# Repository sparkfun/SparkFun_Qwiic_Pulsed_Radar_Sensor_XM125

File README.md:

SparkFun Pulsed Coherent Radar Sensor - Acconeer XM125 (Qwiic)
========================================

[*SparkFun Pulsed Coherent Radar Sensor – Acconeer XM125 (Qwiic) (SEN-24540)*](https://www.sparkfun.com/products/24540)

Forget ultrasonic and infrared sensors; the SparkFun Qwiic Pulsed Coherent Radar Sensor - Acconeer XM125 brings powerful 60 GHz radar technology to your projects. This sensor isn't limited to surface detection; it can see through walls, cabinets, and even pockets (depending on the material), making it perfect for unique applications. Measure distances with millimeter precision, detect motion, the speed of an object, or even gestures!

The XM125 boasts an impressive range of up to 20 meters, allowing you to create long-range sensing projects. The actual measurable distance is dependent on the object size, shape, dielectric properties, and lens (e.g. water level measurements up to 20 meters with lens utilization, human presence detection up to 7 meters with lens-free utilization). Despite its power, the sensor has remarkably low in power consumption, which is ideal for battery-powered applications. The real magic lies in the sensor's ability to do more than measure distance; the XM125 can differentiate between stationary objects and moving targets using pulsed coherent radar. This means you can sense an object's presence and how fast something is moving!

We've included a USB type-C connector, ESD protection diodes on the USB data lines, and a CH340C USB-to-serial converter to connect the XM125 directly to your computer's COM port. Power is regulated down for the XM125 with the AP2112K 3.3V/600mA and RT9080 1.8V/600mA voltage regulators. Buttons for reset and boot are included when resetting the module or setting the board into bootloader mode. Utilizing our handy Qwiic system, no soldering is required to connect it to the rest of your system. However, we still have broken out 0.1in.-spaced pins if you prefer a breadboard.

We've written an Arduino library when the I<sup>2</sup>C presence or distance detection firmware is loaded onto the XM125 module. With the I<sup>2</sup>C presence detection firmware, you can sense when an object is moving in an environment and how far away it is from the sensor. You can detect slow and fast movements with the inter-presence and intra-presence scores, respectively. The I<sup>2</sup>C distance detection firmware is similar to the presence detector by providing distance measurements. However, distance detection will provide information when it detects objects within range. The distance detection firmware can also adjust the sensor's threshold and sensitivity. The read range can also be configured to a certain distance away with either firmware.

Acconeer has also developed a visualization tool written in Python that demonstrates data collection in real time. The [Acconeer Exploration Tool](https://github.com/acconeer/acconeer-python-exploration) is an incredible resource, especially when starting out with the XM125 module to debug and explore the sensor's capabilities. This allows you to fine-tune the sensor for your application. For example, it will graph distance or presence sensing, giving you a count of the number of sweeps, which communication port data is being sent through, and much more. It will also guide you to the optimal sensor settings and help you fine-tune the data processing for your final product implementation. The tool supports Windows and Linux and requires Python version 3.8 or later. This tool is available through their GitHub Repository. Head on over and take a look!

With the SparkFun Qwiic Pulsed Coherent Radar Sensor, a world of new project possibilities opens up. Imagine creating presence detection systems for smart homes and security applications, parking space occupancy detection, gesture recognition interfaces for unique user control, level measurement (for example, in tanks or waste containers), through-wall imaging systems for search and rescue, or even advanced robotics with object avoidance and navigation.

Repository Contents
-------------------

* **.github/workflows** - YAML files used for GitHub Actions and GitHub Pages/mkdocs
* **/Firmware** - Firmware for the XM125 module
* **/Hardware** - Eagle design files (.brd, .sch)
  * **/Production** - Production panel files (.brd)
* **/docs** - Online documentation files
  * **/assets** - Folder containing all the file assets used for product documentation
    * **/board_files** - Copy of design files used for product documentation
    * **/component_documentation** - Datasheets and manuals for hardware components
    * **/img** - Images for product documentation
  * **/github** - Files stating how to contribute and filing issues used for product documentation
  * **/javascript** - Folder containing custom javascript used for product documentation
  * **/stylesheet** - Folder containing CSS files used for product documentation
* **/overrides** - Customization files used for product documentation
  * **/.icons** - Icons used for GitHub used for product documentation
  * **./partials** - Used for product documentation

Documentation
--------------
* **[Library](https://github.com/sparkfun/SparkFun_Qwiic_XM125_Arduino_Library)** - Arduino library for the SparkFun Qwiic Pulsed Coherent Radar Sensor - XM125.
* **[Hookup Guide](https://docs.sparkfun.com/SparkFun_Qwiic_Pulsed_Radar_Sensor_XM125)** - Basic hookup guide for the SparkFUn Qwiic Pulsed Coherent Radar Sensor - XM125.

Product Versions
----------------
* [SEN-24540](https://www.sparkfun.com/products/24540) - Initial Release

Version History
---------------
* V1.0 - Intial Release

License Information
-------------------

This product is _**open source**_! 

Please review the LICENSE.md file for license information. 

If you have any questions or concerns on licensing, please contact technical support on our [SparkFun forums](https://forum.sparkfun.com/viewforum.php?f=152).

Distributed as-is; no warranty is given.

- Your friends at SparkFun.

_<COLLABORATION CREDIT>_

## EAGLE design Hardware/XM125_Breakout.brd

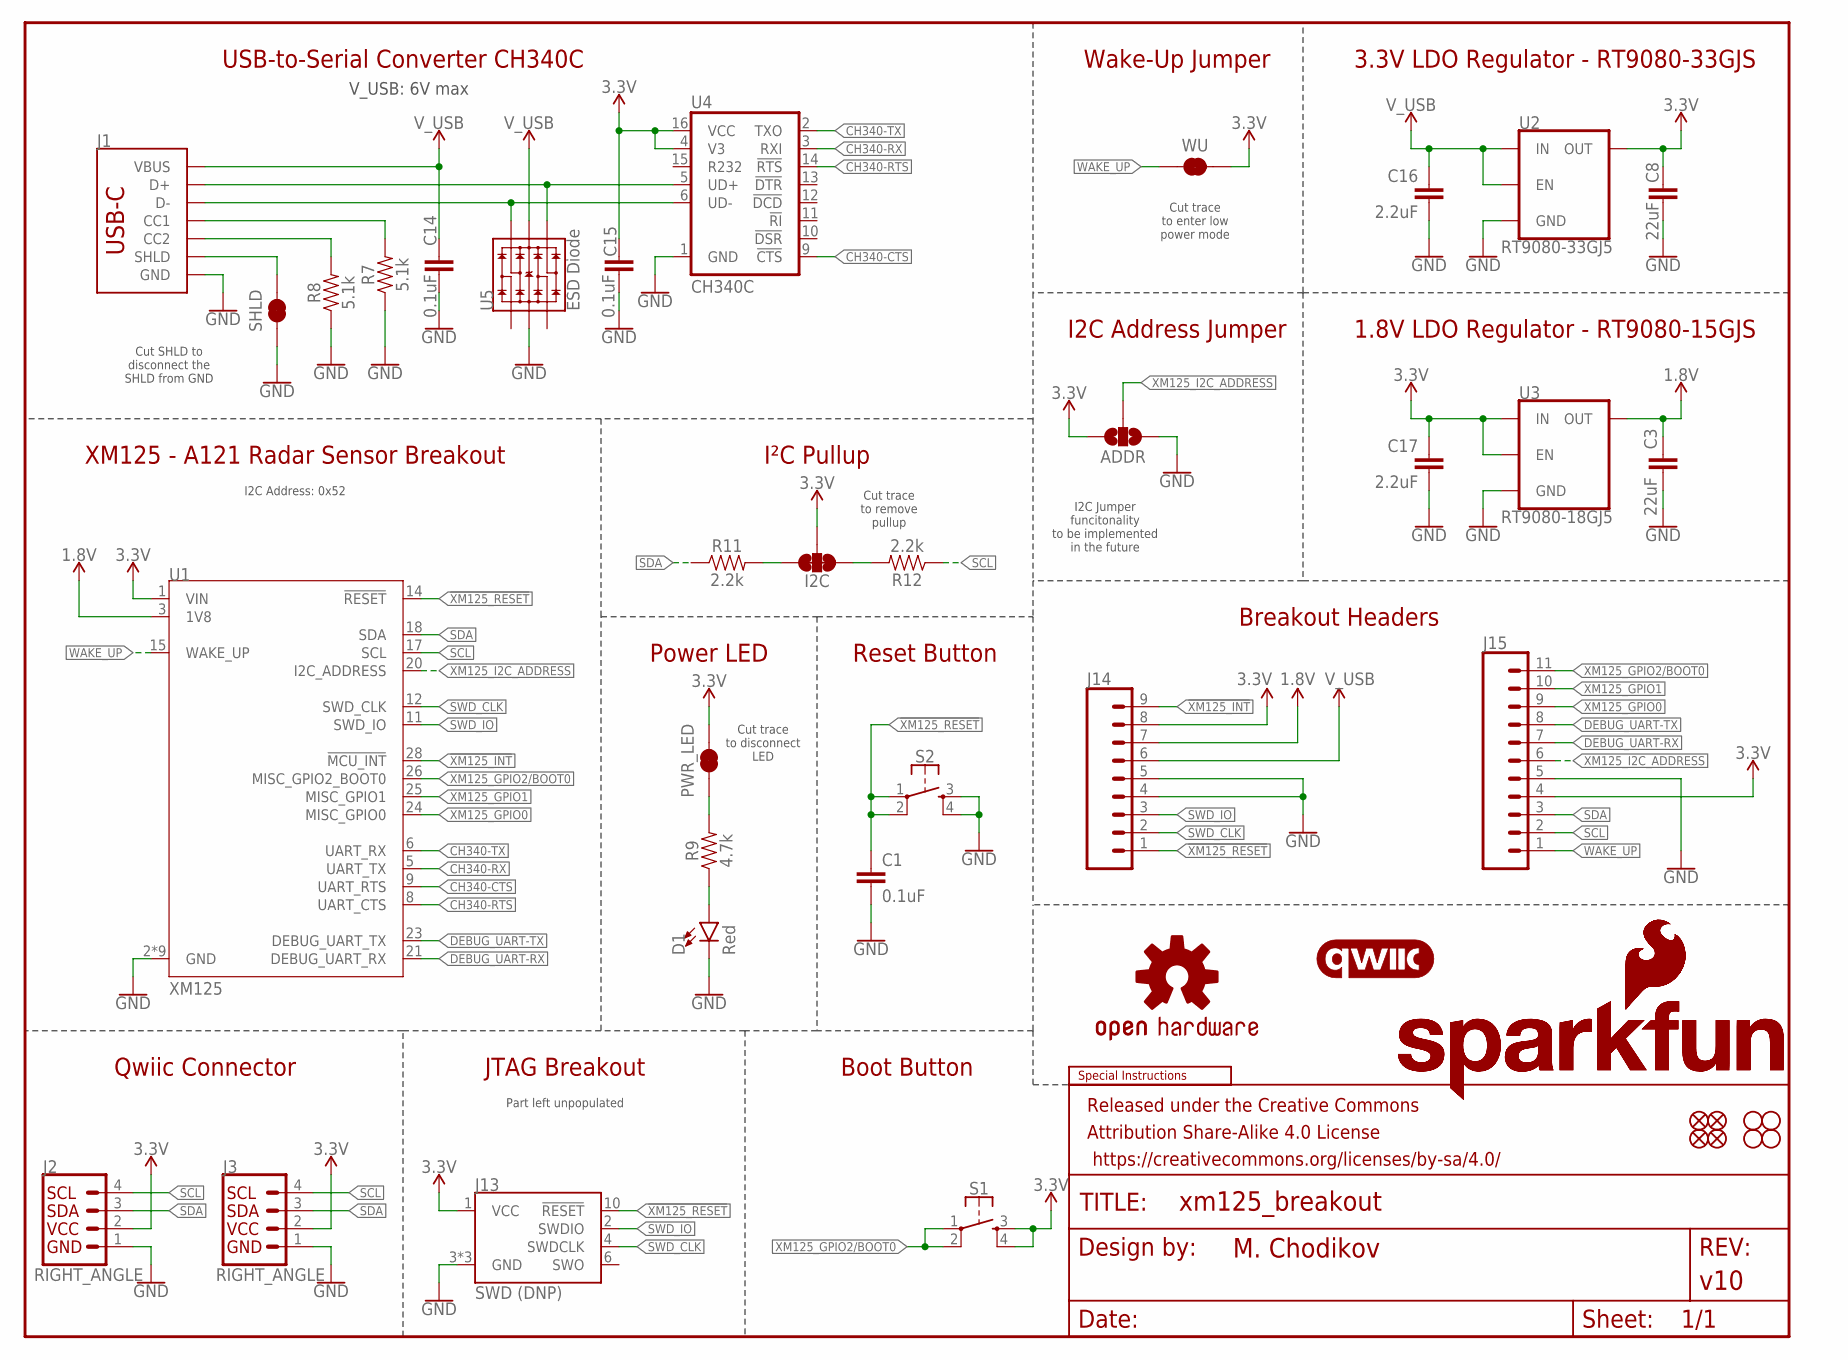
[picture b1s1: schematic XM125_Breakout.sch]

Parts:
ADDR: JUMPER-SMT_3_NO_SILK; SMT-JUMPER_3_NO_SILK
C1, C14, C15: 0.1uF; 0603
C3, C8: 22uF; 0603
C16, C17: 2.2uF; 0603
D1: Red; LED-0603
FD1, FD2, FD3, FD4: FIDUCIAL1X2; FIDUCIAL-1X2
FRAME2: FRAME-LETTER; CREATIVE_COMMONS
H1, H2, H3, H4: STAND-OFF
I2C: JUMPER-SMT_3_2-NC_TRACE_SILK; SMT-JUMPER_3_2-NC_TRACE_SILK
J1: USB_C_2-LAYER_PADS; USB-C-16P-2LAYER-PADS
J2, J3: RIGHT_ANGLE; JST04_1MM_RA
J13: SWD (DNP); 2X5-SMD-UNSHROUDED_DNP_NO_PASTE
J14: CONN_09NO_SILK; 1X09_NO_SILK
J15: CONN_111X11_NO_SILK; 1X11_NO_SILK
LOGO1: SPECIAL_INSTRUCTIONS-ORDERING; ORDERING_INSTRUCTIONS
LOGO2: QWIIC_LOGO_4MM; QWIIC_4MM
LOGO3, LOGO6: SFE_LOGO_NAME_FLAME.1_INCH; SFE_LOGO_NAME_FLAME_.1
LOGO4: OSHW-LOGOS; OSHW-LOGO-S
LOGO5: SFE_LOGO_FLAME.1_INCH; SFE_LOGO_FLAME_.1
PWR_LED: JUMPER-SMT_2_NC_TRACE_SILK; SMT-JUMPER_2_NC_TRACE_SILK
R7, R8: 5.1k; 0603
R9: 4.7k; 0603
R11, R12: 2.2k; 0603
S1, S2: MOMENTARY-SWITCH-SPST-2-SMD-5.2MM; TACTILE_SWITCH_SMD_5.2MM
SHLD: JUMPER-SMT_2_NC_TRACE_SILK; SMT-JUMPER_2_NC_TRACE_SILK
U1: XM125; XM125_ACC
U2: RT9080-33GJ5; SOT23-5
U3: RT9080-18GJ5; SOT23-5
U4: CH340C; SO016
U5: ESD Diode; SOT-23-6
WU: JUMPER-SMT_2_NC_TRACE_SILK; SMT-JUMPER_2_NC_TRACE_SILK

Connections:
1.8V: C3.1, J14.7, U1.3 (1V8), U3.5 (OUT)
3.3V: ADDR.3, C8.1, C15.1, C17.1, I2C.2, J2.2, J3.2, J13.1 (VCC), J14.8, J15.4, PWR_LED.2, S1.3, S1.4, U1.1 (VIN), U2.5 (OUT), U3.1 (IN), U3.3 (EN), U4.4 (V3), U4.16 (VCC), WU.2
!XM125_INT: J14.9, U1.28 (!MCU_INT)
!XM125_RESET: C1.2, J13.10 (!RESET), J14.1, S2.1, S2.2, U1.14 (!RESET)
CH340-CTS: U1.9 (UART_RTS), U4.9 (!CTS)
CH340-RTS: U1.8 (UART_CTS), U4.14 (!RTS)
CH340-RX: U1.5 (UART_TX), U4.3 (RXI)
CH340-TX: U1.6 (UART_RX), U4.2 (TXO)
DEBUG_UART-RX: J15.7, U1.21 (DEBUG_UART_RX)
DEBUG_UART-TX: J15.8, U1.23 (DEBUG_UART_TX)
GND: ADDR.1, C1.1, C3.2, C8.2, C14.2, C15.2, C16.2, C17.2, D1.C, J1.GND, J1.GND2 (GND), J2.1, J3.1, J13.3 (GND), J13.5 (GND), J13.9 (GND), J14.4, J14.5, J15.5, R7.1, R8.1, S2.3, S2.4, SHLD.1, U1.2 (GND), U1.4 (GND), U1.7 (GND), U1.10 (GND), U1.13 (GND), U1.16 (GND), U1.19 (GND), U1.22 (GND), U1.27 (GND), U2.2 (GND), U3.2 (GND), U4.1 (GND), U5.2 (VSS)
unnamed: J1.A6 (D+), J1.B6 (D+), U4.5 (UD+), U5.4 (IO3)
unnamed: J1.A7 (D-), J1.B7 (D-), U4.6 (UD-), U5.6 (IO4)
unnamed: J1.SHLD1 (SHLD), J1.SHLD2 (SHLD), J1.SHLD3 (SHLD), J1.SHLD4 (SHLD), SHLD.2
unnamed: J1.B5 (CC2), R8.2
unnamed: J1.A5 (CC1), R7.2
unnamed: PWR_LED.1, R9.2
unnamed: D1.A, R9.1
unnamed: I2C.3, R11.2
unnamed: I2C.1, R12.2
SCL: J2.4, J3.4, J15.2, R12.1, U1.17 (SCL)
SDA: J2.3, J3.3, J15.3, R11.1, U1.18 (SDA)
SWD_CLK: J13.4 (SWDCLK), J14.2, U1.12 (SWD_CLK)
SWD_IO: J13.2 (SWDIO), J14.3, U1.11 (SWD_IO)
V_USB: C14.1, C16.1, J1.VBUS1 (VBUS), J1.VBUS2 (VBUS), J14.6, U2.1 (IN), U2.3 (EN), U5.5 (VCC)
WAKE_UP: J15.1, U1.15 (WAKE_UP), WU.1
XM125_GPIO0: J15.9, U1.24 (MISC_GPIO0)
XM125_GPIO1: J15.10, U1.25 (MISC_GPIO1)
XM125_GPIO2/BOOT0: J15.11, S1.1, S1.2, U1.26 (MISC_GPIO2_BOOT0)
XM125_I2C_ADDRESS: ADDR.2, J15.6, U1.20 (I2C_ADDRESS)

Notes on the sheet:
USB-to-Serial Converter CH340C
1.8V LDO Regulator - RT9080-15GJS
3.3V LDO Regulator - RT9080-33GJS
XM125 - A121 Radar Sensor Breakout
Qwiic Connector
Power LED
Breakout Headers
I²C Pullup
Cut trace to remove pullup
Boot Button
Cut trace to disconnect LED
I2C Address: 0x52
JTAG Breakout
Part left unpopulated
Wake-Up Jumper
I2C Address Jumper
Reset Button
V_USB: 6V max
Cut trace to enter low power mode
I2C Jumper funcitonality to be implemented in the future
Cut SHLD to disconnect the SHLD from GND

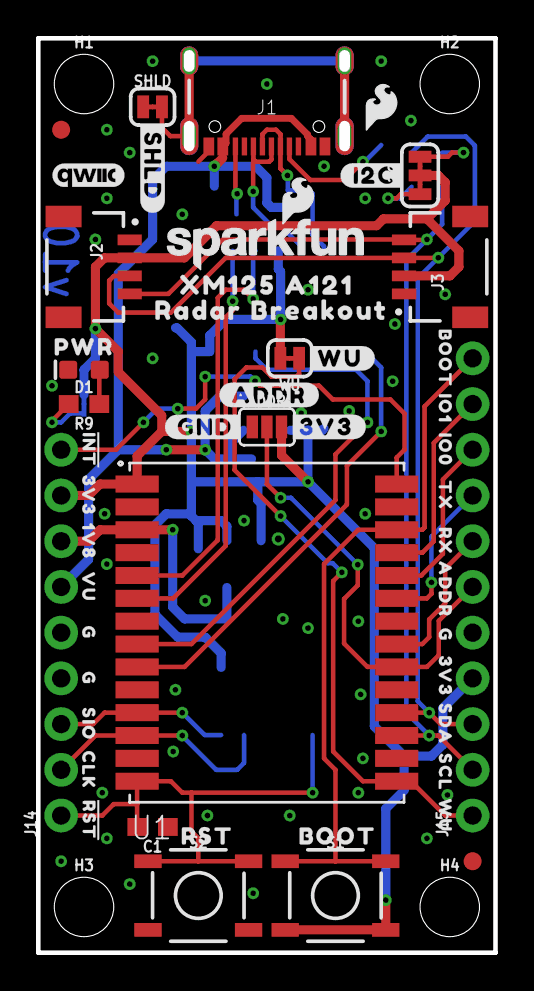
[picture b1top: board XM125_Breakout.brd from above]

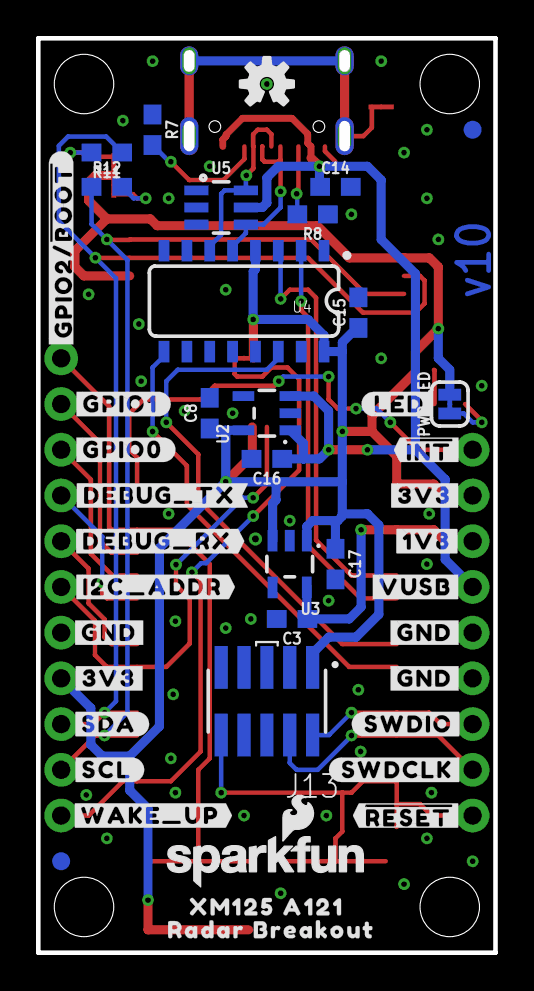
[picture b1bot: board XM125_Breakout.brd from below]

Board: 2 copper layers, 25.4 x 50.8 mm, 100 parts (43 on the bottom side), 30 nets.

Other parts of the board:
U$1: #INT143
U$2: ##INT#2
U$3: #LED#139
U$4, U$30, U$31: #GND#141
U$5: RST1630063003525
U$6: RX1152
U$7: #SWDIO#4
U$8: #VUSB#1
U$9: #3V3#17
U$10: #SCL#8
U$11: BOOT21630063003532
U$12: PWR21630063003533
U$13: #SDA#9
U$14, U$33: 3V3144
U$15: 1V8144
U$16: #1V8#141
U$17: RADAR_BREAKOUT1163
U$18: WU9
U$19: #RST6
U$20: #GPIO0#5
U$21: #GPIO1#5
U$22: #WU#14
U$23, U$32: #3V3#141
U$24: XM125_A1211163
U$25: #ADDR#16
U$26: #I2C#126
U$27: #GPIO2##BOOT#141
U$28: #DEBUG_RX#19
U$29: #SHLD#129
U$34, U$35, U$36: G144
U$38: VU146
U$39: IO0147
U$40: IO1148
U$41: BOOT1149
U$42: CLK1150
U$43: #SWDCLK#1151
U$44: TX1153
U$45: ADDR1154
U$46: SDA1155
U$47: SCL1157
U$48: #I2C_ADDR#12
U$49: SIO1159
U$50: #GND#17
U$51: #DEBUG_TX#18
U$53: RADAR_BREAKOUT1166
U$54: XM125_A1211167
U$55: #WAKE_UP#12
U$56: ##RESET#13

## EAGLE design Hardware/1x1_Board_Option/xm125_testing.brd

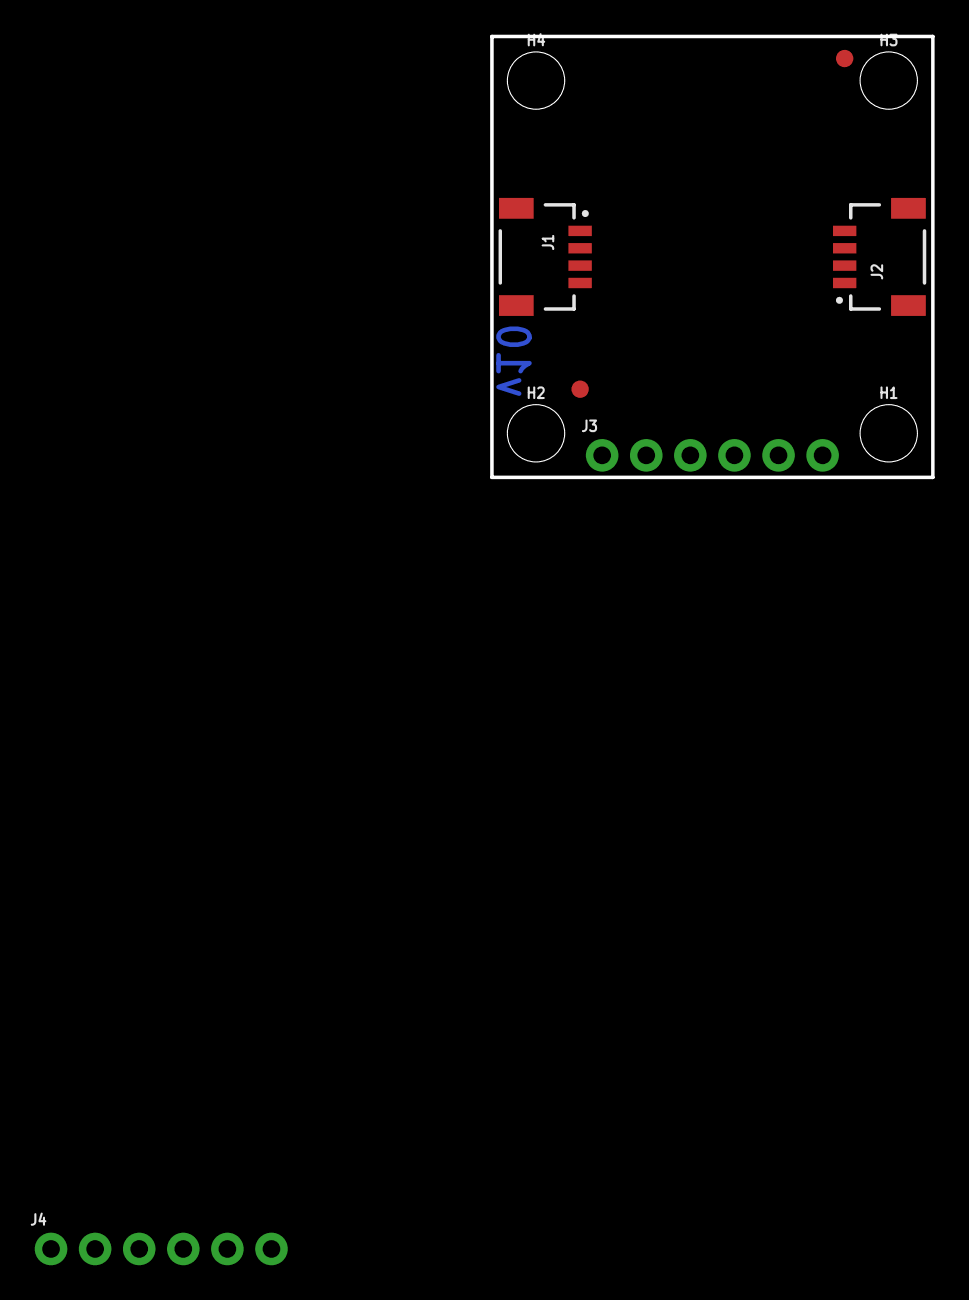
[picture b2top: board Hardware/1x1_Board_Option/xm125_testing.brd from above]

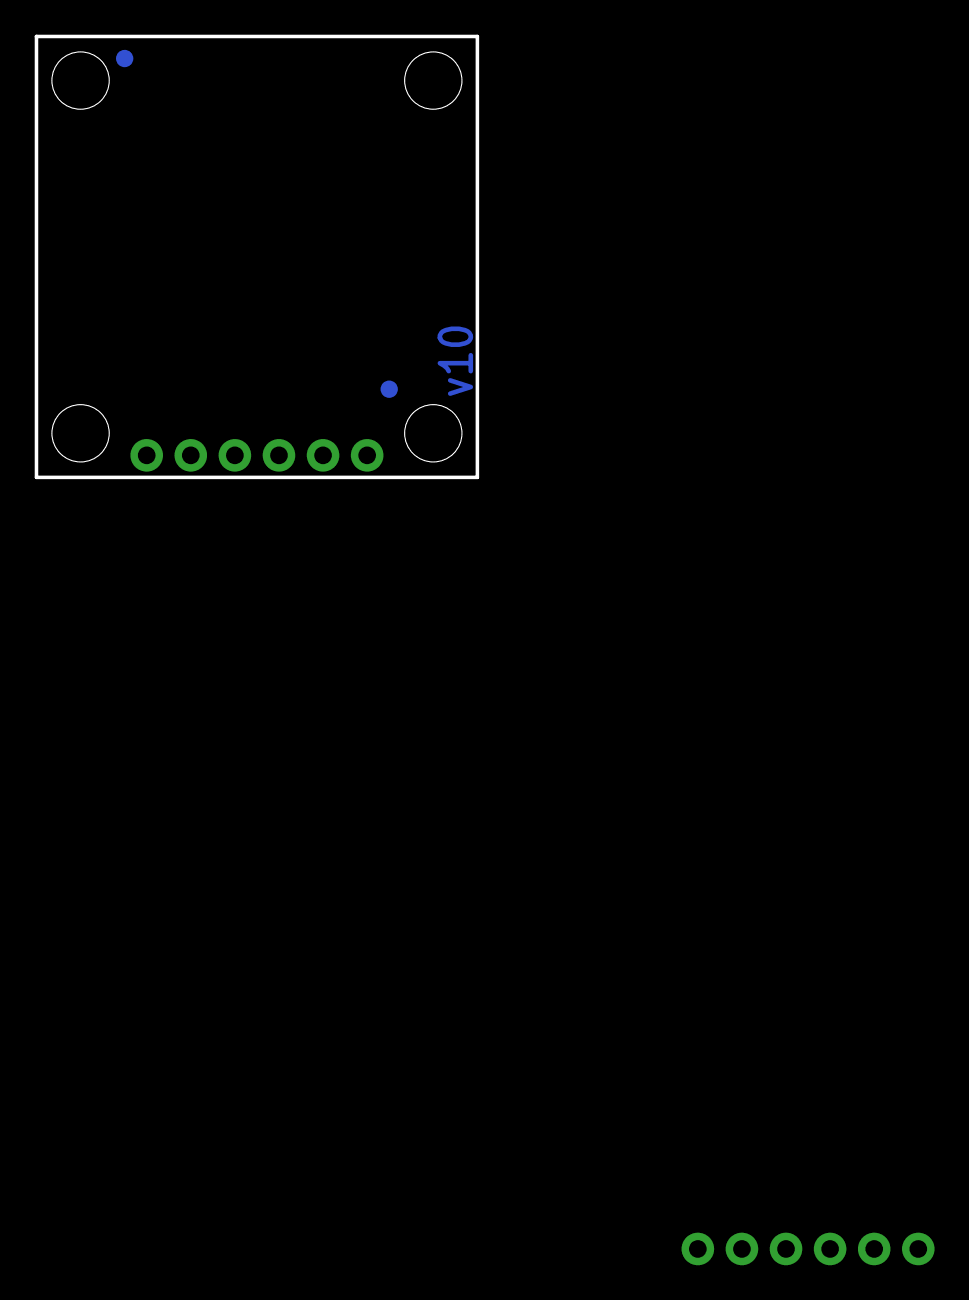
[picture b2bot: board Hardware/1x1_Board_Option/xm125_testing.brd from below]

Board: 2 copper layers, 25.4 x 25.4 mm, 22 parts (6 on the bottom side), 2 nets, no tracks yet.

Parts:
FD1, FD2, FD3, FD4: FIDUCIAL1X2; FIDUCIAL-1X2
FRAME1: FRAME-LETTER; CREATIVE_COMMONS
H1, H2, H3, H4: STAND-OFF
J1, J2: QWIIC_RIGHT_ANGLE; JST04_1MM_RA
J3, J4: 1X06_NO_SILK
LOGO1: OSHW-LOGOS; OSHW-LOGO-S
LOGO2: SFE_LOGO_NAME_FLAME.1_INCH; SFE_LOGO_NAME_FLAME_.1
LOGO3: QWIIC_LOGO_4MM; QWIIC_4MM
LOGO4: SFE_LOGO_NAME8_MM; SFE_LOGO_NAME_8MM
LOGO5: SPECIAL_INSTRUCTIONS-ORDERING; ORDERING_INSTRUCTIONS
LOGO6: SFE_LOGO_FLAME.1_INCH; SFE_LOGO_FLAME_.1
U$6: #INT#5289
U$7: PWR41
U$10: #I�C#0

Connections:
1: J1.1, J2.1
2: J1.2, J2.2

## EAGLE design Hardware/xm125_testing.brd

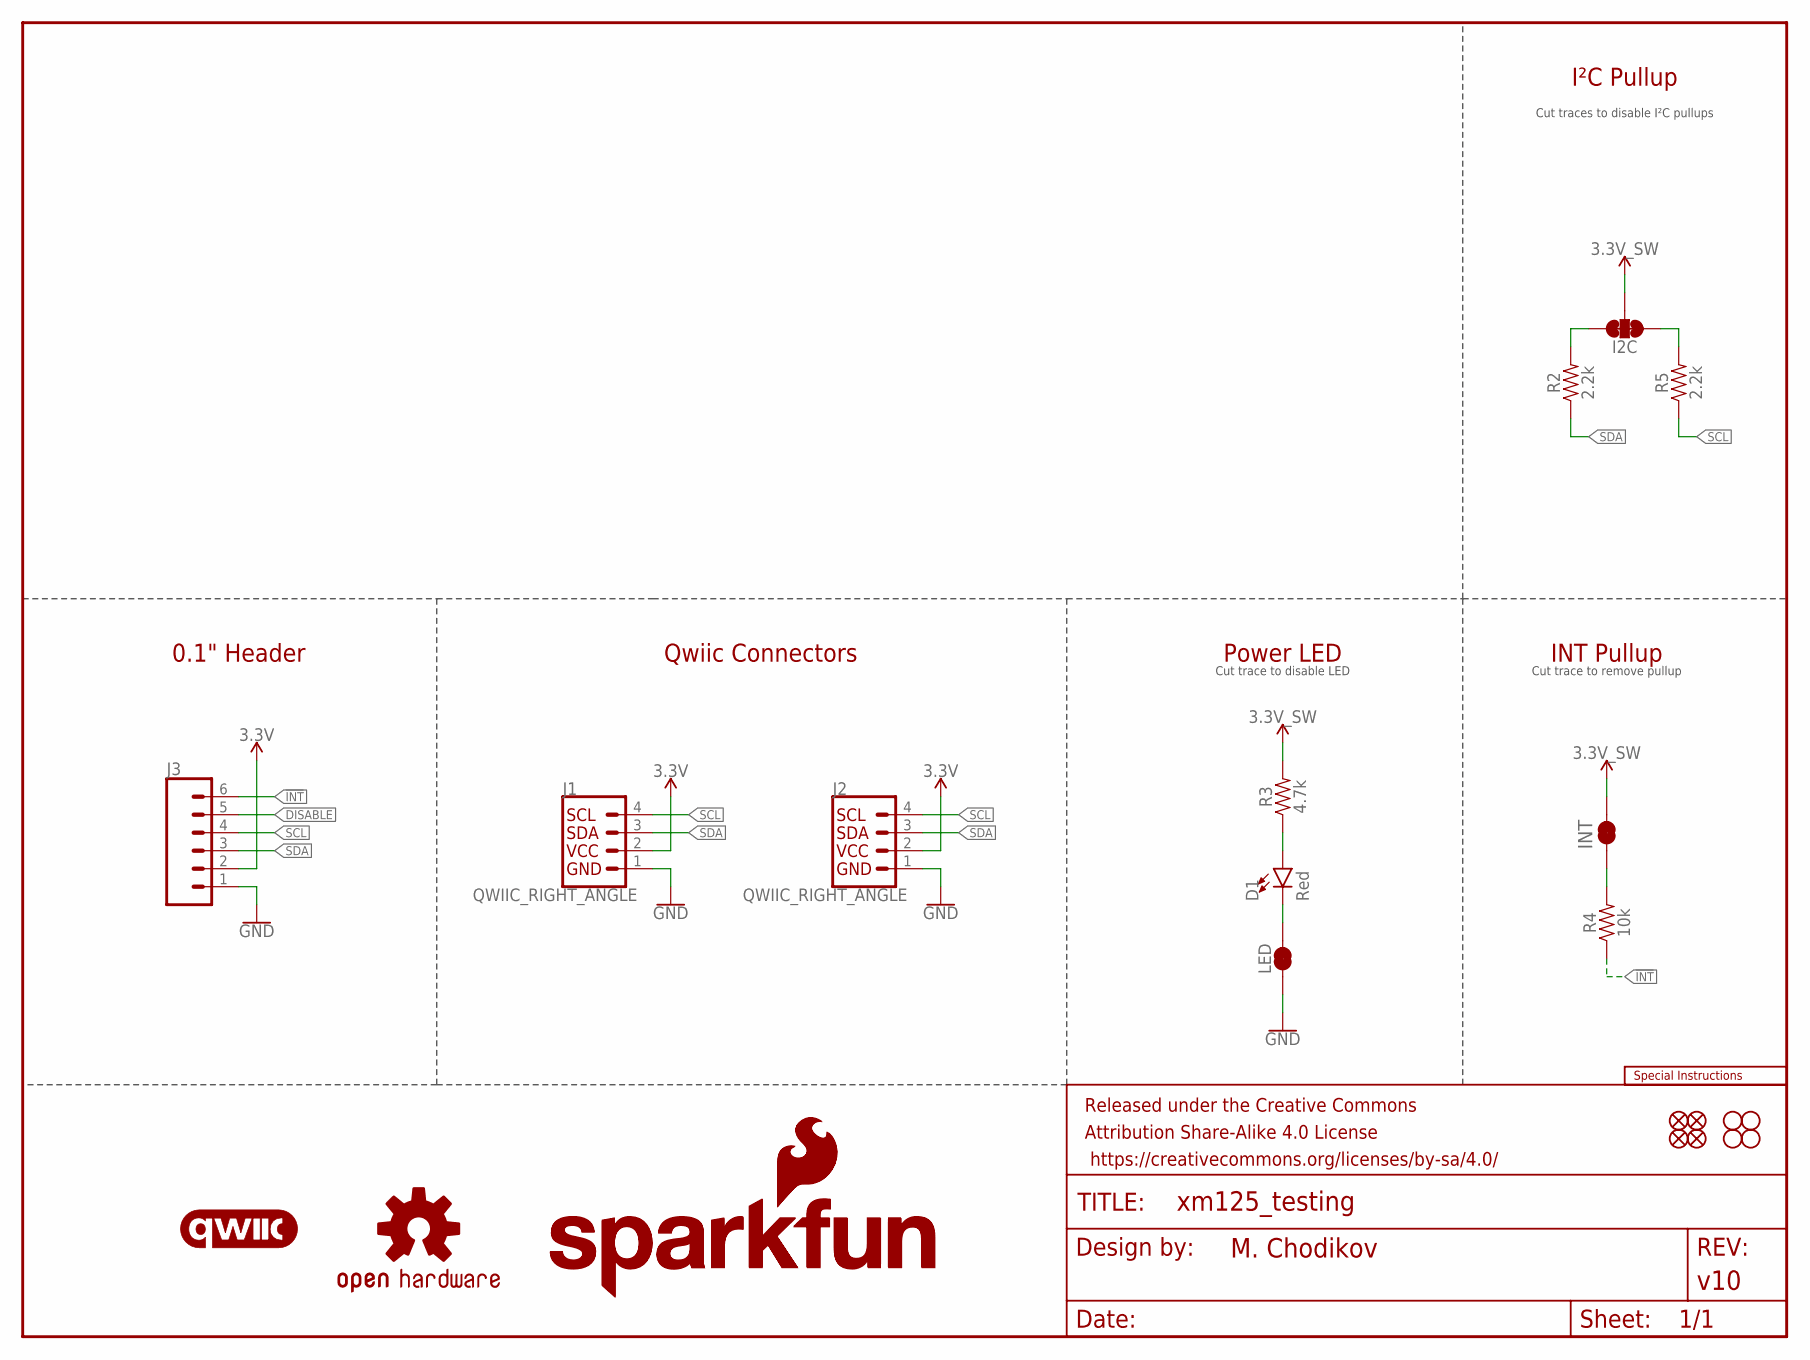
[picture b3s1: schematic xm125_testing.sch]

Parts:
D1: Red; LED-0603
FD1, FD2, FD3, FD4: FIDUCIAL1X2; FIDUCIAL-1X2
FRAME1: FRAME-LETTER; CREATIVE_COMMONS
H1, H2, H3, H4: STAND-OFF
I2C: JUMPER-SMT_3_2-NC_TRACE_SILK; SMT-JUMPER_3_2-NC_TRACE_SILK
J1, J2: QWIIC_RIGHT_ANGLE; JST04_1MM_RA
J3: CONN_06NO_SILK_FEMALE_PTH; 1X06_NO_SILK
JP2: JUMPER-SMT_2_NC_TRACE_SILK; SMT-JUMPER_2_NC_TRACE_SILK
LED: JUMPER-SMT_2_NC_TRACE_SILK; SMT-JUMPER_2_NC_TRACE_SILK
LOGO1: OSHW-LOGOS; OSHW-LOGO-S
LOGO2: SFE_LOGO_NAME_FLAME.1_INCH; SFE_LOGO_NAME_FLAME_.1
LOGO3: QWIIC_LOGO_4MM; QWIIC_4MM
LOGO4: SFE_LOGO_NAME8_MM; SFE_LOGO_NAME_8MM
LOGO5: SPECIAL_INSTRUCTIONS-ORDERING; ORDERING_INSTRUCTIONS
LOGO6: SFE_LOGO_FLAME.1_INCH; SFE_LOGO_FLAME_.1
R2, R5: 2.2k; 0603
R3: 4.7k; 0603
R4: 10k; 0603

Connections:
3.3V: J1.2, J2.2, J3.2
3.3V_SW: I2C.2, JP2.2, R3.2
!INT: J3.6, R4.1
DISABLE: J3.5
GND: J1.1, J2.1, J3.1, LED.1
unnamed: D1.C, LED.2
unnamed: I2C.3, R2.2
unnamed: D1.A, R3.1
unnamed: JP2.1, R4.2
unnamed: I2C.1, R5.2
SCL: J1.4, J2.4, J3.4, R5.1
SDA: J1.3, J2.3, J3.3, R2.1

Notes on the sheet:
I²C Pullup
Cut traces to disable I²C pullups
Cut trace to disable LED
Power LED
Cut trace to remove pullup
INT Pullup
0.1" Header
Qwiic Connectors
INT

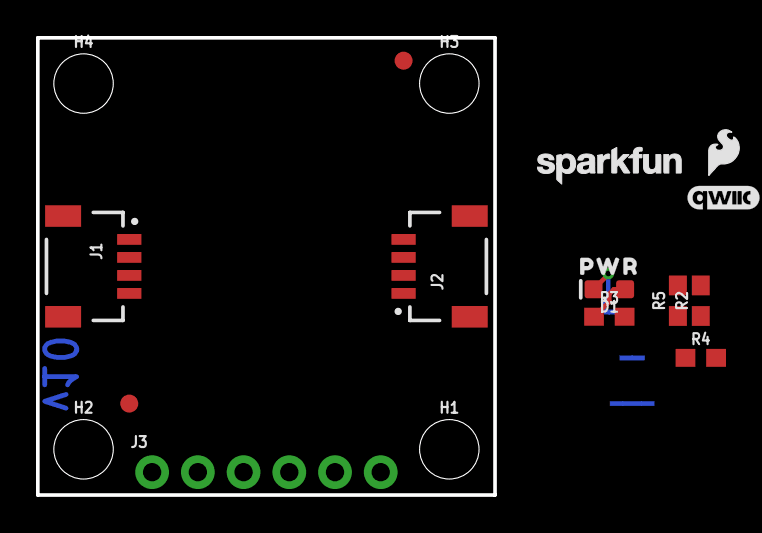
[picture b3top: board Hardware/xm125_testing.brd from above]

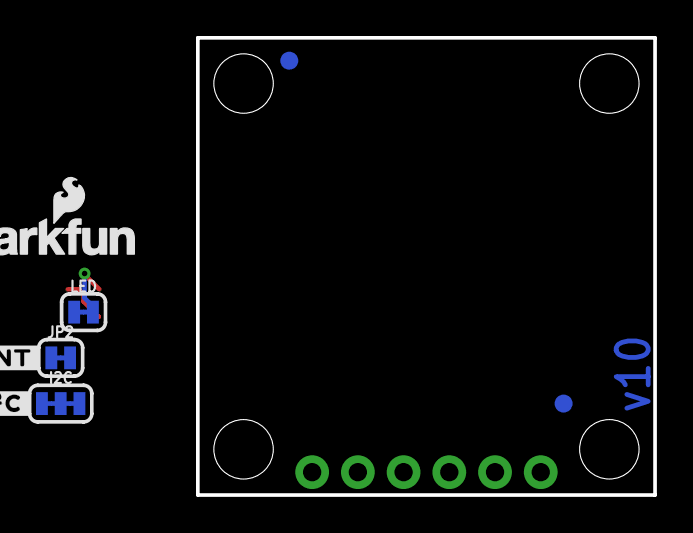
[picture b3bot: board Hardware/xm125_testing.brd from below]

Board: 2 copper layers, 25.4 x 25.4 mm, 29 parts (9 on the bottom side), 11 nets.

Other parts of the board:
U$6: #INT#5289
U$7: PWR41
U$10: #I�C#0

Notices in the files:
parts and their libraries:
SparkFun-Aesthetics: Licensing: Creative Commons ShareAlike 4.0 International - https://creativecommons.org/licenses/by-sa/4.0
SparkFun-Aesthetics: Released under the Creative Commons Attribution Share-Alike 4.0 License
SparkFun-Aesthetics: https://creativecommons.org/licenses/by-sa/4.0
